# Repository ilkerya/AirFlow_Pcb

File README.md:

# AirFlow_Pcb
AirFlow Sensor PCB files made with https://www.kicad.org/

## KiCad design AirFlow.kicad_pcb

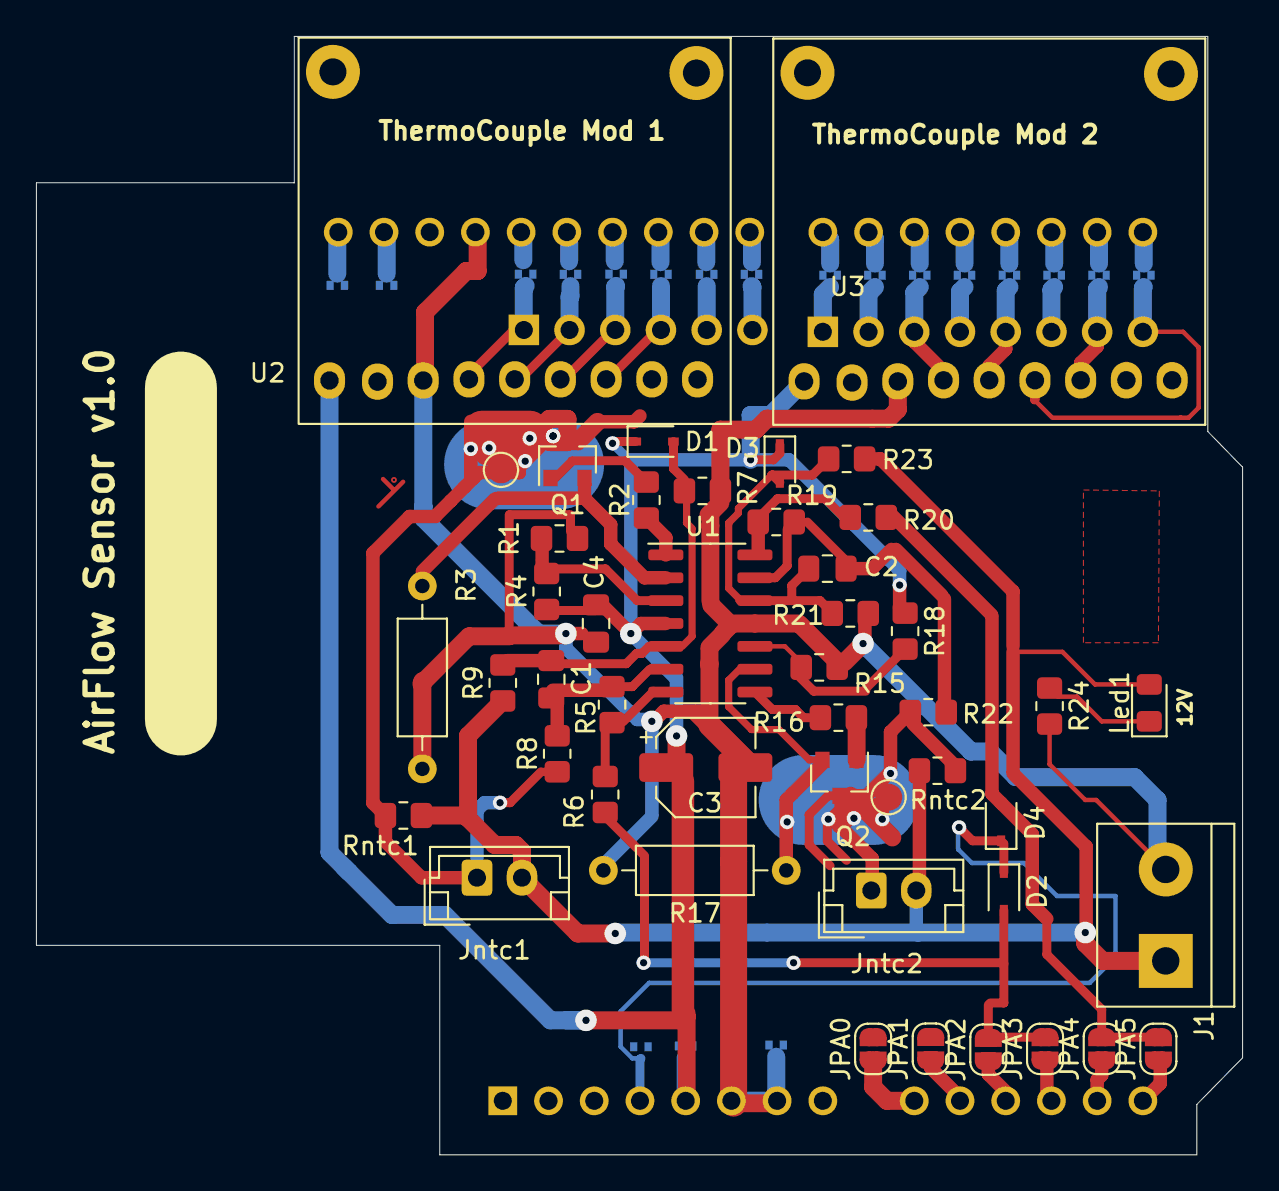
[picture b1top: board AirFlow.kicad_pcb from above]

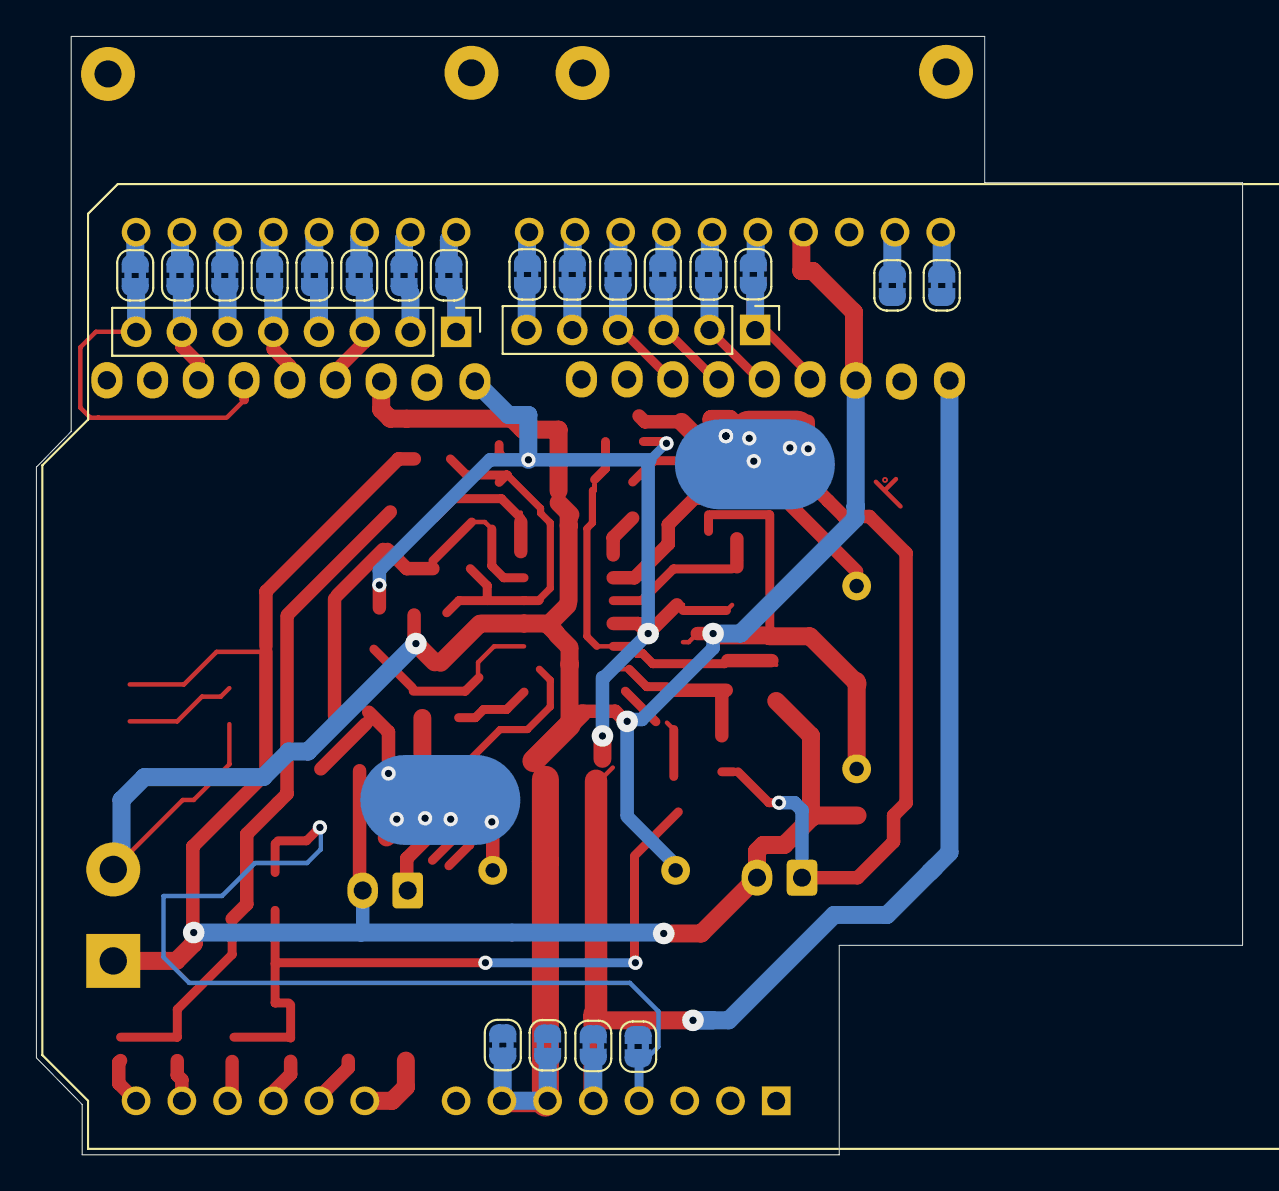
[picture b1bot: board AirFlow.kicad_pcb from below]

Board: 2 copper layers, 67.0 x 62.1 mm, 69 parts (23 on the bottom side), 59 nets.

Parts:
A1: Arduino_UNO_R3
C1, C2, C4: 10nF; C_0805_2012Metric_Pad1.18x1.45mm_HandSolder
C3: 10uF; CP_Elec_5x5.4
D1, D2, D3, D4: 1N4148WS; D_SOD-323
J1: Screw_Terminal_01x02; TerminalBlock_bornier-2_P5.08mm
J5: Conn_01x08_MountingPin; PinHeader_1x08_P2.54mm_Vertical
J6: Conn_01x06_MountingPin; PinHeader_1x06_P2.54mm_Vertical
JP0, JP1, JP2, JP3, JP3V3, JP4, JP5, JP5V1, JP6, JP7, JP8, JP9, JP10, JP11, JP12, JP13: SolderJumper_2_Bridged; SolderJumper-2_P1.3mm_Bridged2Bar_RoundedPad1.0x1.5mm
JPA0, JPA1, JPA2, JPA3, JPA4, JPA5: SolderJumper_2_Bridged; SolderJumper-2_P1.3mm_Open_RoundedPad1.0x1.5mm
JPGND1, JPGND2: SolderJumper_2_Bridged; SolderJumper-2_P1.3mm_Bridged2Bar_RoundedPad1.0x1.5mm
JP_SCL1: SolderJumper_2_Bridged; SolderJumper-2_P1.3mm_Bridged2Bar_RoundedPad1.0x1.5mm
JP_SDA1: SolderJumper_2_Bridged; SolderJumper-2_P1.3mm_Bridged2Bar_RoundedPad1.0x1.5mm
Jntc1, Jntc2: Conn_01x02; JST_EH_B2B-EH-A_1x02_P2.50mm_Vertical
Led1: LED; LED_0805_2012Metric_Pad1.15x1.40mm_HandSolder
Q1, Q2: IRLML2060; SOT-23
R1, R15: 860R; R_0805_2012Metric_Pad1.20x1.40mm_HandSolder
R2, R16: 470R; R_0805_2012Metric_Pad1.20x1.40mm_HandSolder
R3, R17: 60R; R_Axial_DIN0207_L6.3mm_D2.5mm_P10.16mm_Horizontal
R4, R18: 3K9; R_0805_2012Metric_Pad1.20x1.40mm_HandSolder
R5, R7, R19, R21: 82K; R_0805_2012Metric_Pad1.20x1.40mm_HandSolder
R6, R20: 1K; R_0805_2012Metric_Pad1.20x1.40mm_HandSolder
R8, R9, R22, R23: 22K; R_0805_2012Metric_Pad1.20x1.40mm_HandSolder
R24: 10K; R_0805_2012Metric_Pad1.20x1.40mm_HandSolder
Rntc1, Rntc2: 150R; R_0805_2012Metric_Pad1.20x1.40mm_HandSolder
TP1, TP2: TestPoint; TestPoint_Pad_D1.5mm
U1: MCP6004; SOIC-14_3.9x8.7mm_P1.27mm
U2, U3: Adafruit_ThermoModule; Thermo_Int_Adafruit2

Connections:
+3V3: A1.4, D2.1, D4.1, JP3V3.1
+5V: A1.5, C3.1, C4.1, D1.1, D3.1, JP5V1.1, R4.1, R18.1, U1.4, U2.9, U3.9
+12V: J1.1, Jntc1.2, Jntc2.2, Led1.2, R9.1, R23.1, Rntc1.1, Rntc2.1
D0: J5.8, JP0.1, U3.4
D1: J5.7, JP1.1, U3.3
D2: J5.6, JP2.1
D3: J5.5, JP3.1, U3.5
D4: J5.4, JP4.1
D5: J5.3, JP5.1, U3.6
D6: J5.2, JP6.1
D7: J5.1, JP7.1
D8: J6.6, JP8.1
D9: J6.5, JP9.1
D10: J6.4, JP10.1, U2.3
D11: J6.3, JP11.1, U2.4
D12: J6.2, JP12.1, U2.5
D13: J6.1, JP13.1, U2.6
GND: A1.6, A1.7, A1.29, C3.2, C4.2, J1.2, JPGND1.1, JPGND2.1, R1.2, R3.2, R7.2, R15.2, R17.2, R21.2, R24.2, U1.11, U2.7, U3.7
unnamed: A1.9, JPA0.1
unnamed: A1.10, JPA1.1
unnamed: A1.11, JPA2.1
unnamed: A1.12, JPA3.1
unnamed: A1.13, JPA4.1
unnamed: A1.14, JPA5.1
unnamed: A1.15, JP0.2
unnamed: A1.16, JP1.2
unnamed: A1.17, JP2.2
unnamed: A1.18, JP3.2
unnamed: A1.19, JP4.2
unnamed: A1.20, JP5.2
unnamed: A1.21, JP6.2
unnamed: A1.22, JP7.2
unnamed: A1.23, JP8.2
unnamed: A1.24, JP9.2
unnamed: A1.25, JP10.2
unnamed: A1.26, JP11.2
unnamed: A1.27, JP12.2
unnamed: A1.28, JP13.2
unnamed: A1.31, JP_SDA1.1
unnamed: A1.32, JP_SCL1.1
unnamed: C1.1, D1.2, R7.1, R9.2, U1.5
unnamed: C1.2, R5.1, R8.2, U1.6
unnamed: C2.1, D3.2, R21.1, R23.2, U1.12
unnamed: C2.2, R19.1, R22.2, U1.13
unnamed: Jntc1.1, Q1.3, R8.1, Rntc1.2, TP1.1
unnamed: Jntc2.1, Q2.3, R22.1, Rntc2.2, TP2.1
unnamed: Led1.1, R24.1
unnamed: Q1.1, R2.2
unnamed: Q1.2, R3.1, U1.2
unnamed: Q2.1, R16.2
unnamed: Q2.2, R17.1, U1.9
unnamed: R1.1, R4.2, U1.3
unnamed: R2.1, U1.1
unnamed: R5.2, R6.1, U1.7
unnamed: R15.1, R18.2, U1.10
unnamed: R16.1, U1.8
unnamed: R19.2, R20.1, U1.14
Out1: D2.2, JPA2.2, JPA3.2, R6.2
Out2: D4.2, JPA4.2, JPA5.2, R20.2

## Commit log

2021-06-07 fixes
